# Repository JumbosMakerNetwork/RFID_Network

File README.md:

# Jumbo's Maker Network - RFID Usage Tracking
This project is an RFID tag and arduino based system for tracking use in a makerspace while also integrating automated safety interlocks through use of data and power relays. 

This includes the firmware and hardware files for the system as well as a series of analytical software used to derive insightful data from the makerspace.

This project is currently in development, so if you stumble across this, please let us know if something doesn't work and feel free to comment to help out if you have some useful feedback.

## Hardware
Contains:
	-Eagle Files, used as design for fabricating circuit boards. There are a variety of circuit boards used in this project, the principal ones being a data interlock board used to interrupt serial communication between devices, and a Pro Shield board, which is used to connect all the components of the RFID reader (e.g. the Mifare Scanner, the LCD monitor..) to the Arduino ESP8266
	-Enclosure files, which are CAD schematics for 3d printing/laser cutting the enclosure that holds all the components

## Scripts
Contains:
	-Several scripts used to initialize new stations and users. These funcitons will eventually be encapsulated by a unified Python data model which will be used for all SQL functions.

## Source Code
Contains:
	-Arduino: the necessary libraries and source code needed for the Arduino microcontrollers powering this system. Within this repo are folders for Signin and Relay stations; Signin stations only have the funcitnality of signin/signout, whereas the relay terminals are capable of restricting power or serial communication between devices.
	-All the php and PSQL initialization tools used to create our PSQL database (in scripts and www)

## Web Analytics
Contains:
	-a set of documents that generate an HTML page featuring visualized data of makerspace usage and new membership over time. This data is collected with python scripts using the pyscopg module, and then interpreted with javascript files utilizing ajax and jquery, finally being visualized with the charts.js library.

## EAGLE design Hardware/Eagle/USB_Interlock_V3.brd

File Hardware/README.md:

# CEEO Makerspace Data Collection - Hardware

## Description
This will be for all the drawings for RFID fobs, terminal enclosures, and PCBs that support the system. 

## To Dos
- ~~ Design Enclosures ~~
- ~~ Finish PCBs ~~
- ~~ Design some RFID key fobs ~~
- ~~ Add Bill of Materials ~~

## Notes

Notes go here

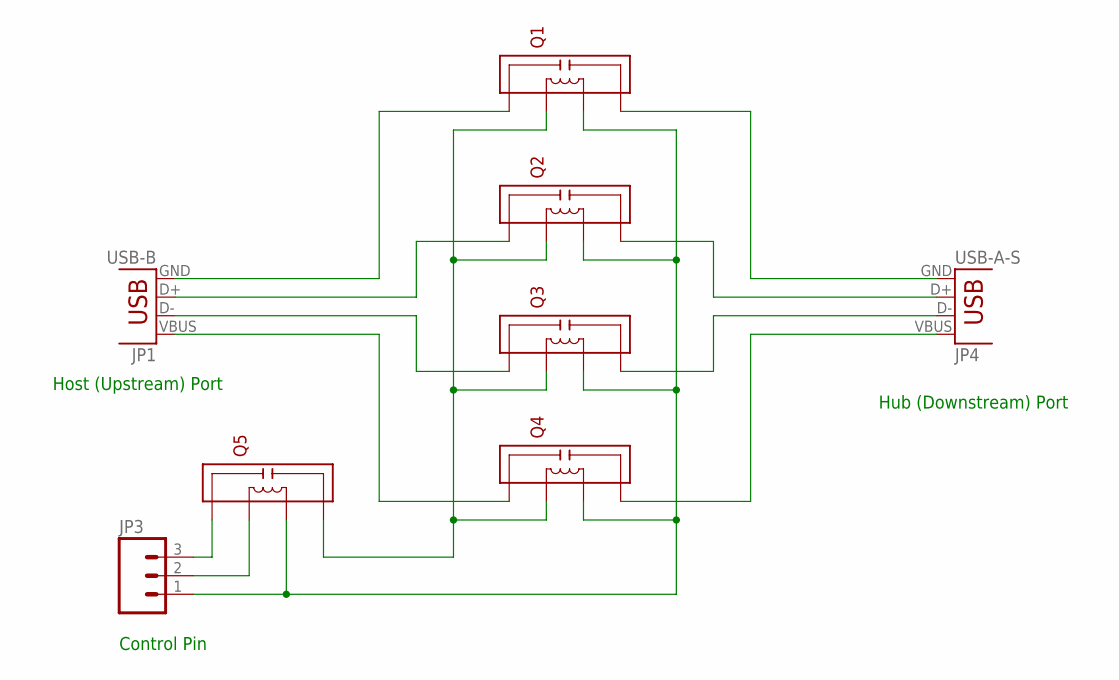
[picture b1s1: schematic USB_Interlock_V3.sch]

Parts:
JP1: USB-B; USB-B-PTH
JP3: M03LONGPADS; 1X03_LONGPADS
JP4: USB-A-S
Q1, Q2, Q3, Q4, Q5: 9007-12-01

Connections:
GND: JP3.1, Q1.P$3, Q2.P$3, Q3.P$3, Q4.P$3, Q5.P$3
HV1: JP4.D-, Q3.P$4
HV2: JP4.D+, Q2.P$4
LV1: JP1.D-, Q3.P$1
LV2: JP1.D+, Q2.P$1
unnamed: JP3.3, Q5.P$1
unnamed: JP3.2, Q5.P$2
unnamed: Q1.P$2, Q2.P$2, Q3.P$2, Q4.P$2, Q5.P$4
unnamed: JP1.GND, Q1.P$1
unnamed: JP4.GND, Q1.P$4
unnamed: JP1.VBUS, Q4.P$1
V1: JP4.VBUS, Q4.P$4

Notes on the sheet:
Hub (Downstream) Port
Host (Upstream) Port
Control Pin

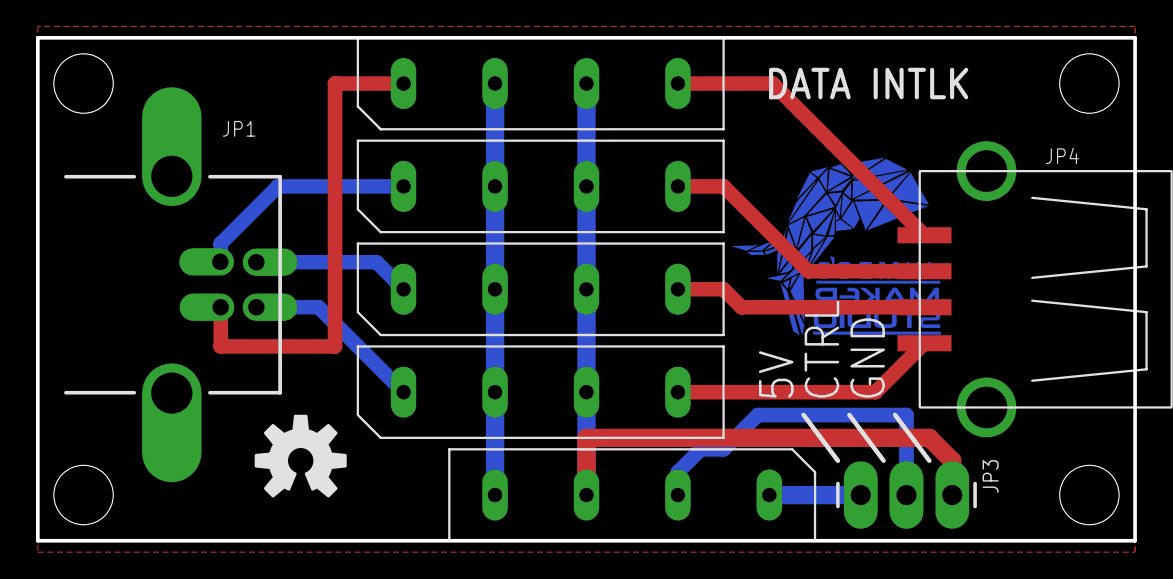
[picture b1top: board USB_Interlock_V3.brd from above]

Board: 2 copper layers, 61.0 x 27.9 mm, 14 parts (1 on the bottom side), 12 nets.

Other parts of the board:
U$1: OSHW-LOGO-M
U$2, U$3, U$4, U$5: STAND-OFF
U$7: JMS_LOG_COPPER

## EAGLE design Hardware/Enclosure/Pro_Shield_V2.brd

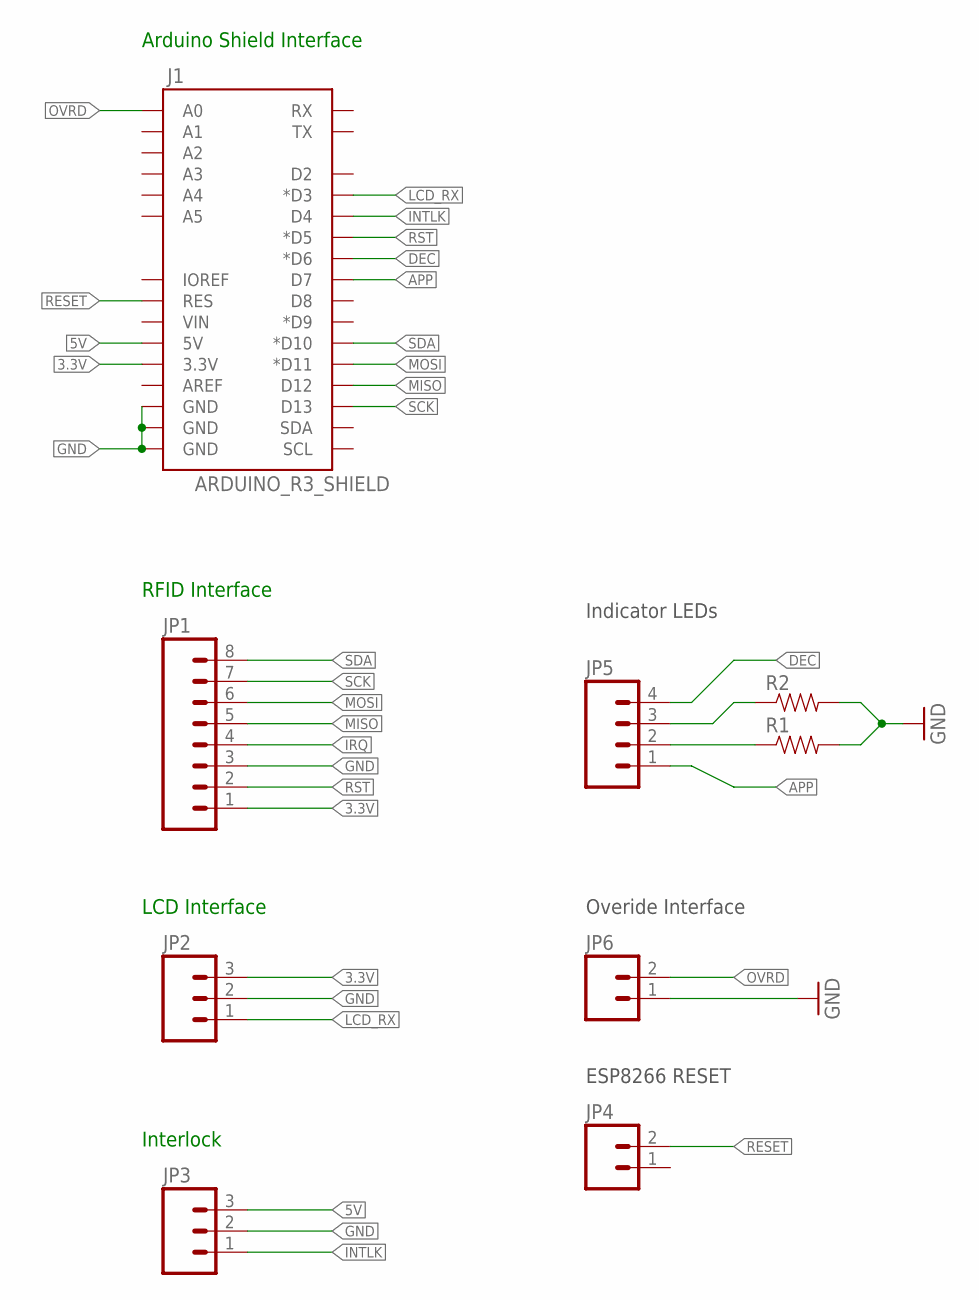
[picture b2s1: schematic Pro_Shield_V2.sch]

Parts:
J1: ARDUINO_R3_SHIELD; UNO_R3_SHIELD
JP1: M08LONGPADS; 1X08_LONGPADS
JP2, JP3: M03LONGPADS; 1X03_LONGPADS
JP4, JP6: M02LOCK_LONGPADS; 1X02_LOCK_LONGPADS
JP5: M04LONGPADS; 1X04_LONGPADS
R1, R2: RESISTORPTH-1/4W; AXIAL-0.4

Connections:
3.3V: J1.3.3V, JP1.1, JP2.3
5V: J1.5V, JP3.3
APP: J1.D7, JP5.1
DEC: J1.D6 (*D6), JP5.4
GND: J1.GND@0 (GND), J1.GND@1 (GND), J1.GND@2 (GND), JP1.3, JP2.2, JP3.2, JP6.1, R1.P$2 (2), R2.P$2 (2)
INTLK: J1.D4, JP3.1
IRQ: JP1.4
LCD_RX: J1.D3 (*D3), JP2.1
MISO: J1.D12, JP1.5
MOSI: J1.D11 (*D11), JP1.6
unnamed: JP5.2, R1.P$1 (1)
unnamed: JP5.3, R2.P$1 (1)
OVRD: J1.A0, JP6.2
RESET: J1.RES, JP4.2
RST: J1.D5 (*D5), JP1.2
SCK: J1.D13, JP1.7
SDA: J1.D10 (*D10), JP1.8

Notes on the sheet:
LCD Interface
RFID Interface
Arduino Shield Interface
Indicator LEDs
Overide Interface
Interlock
ESP8266 RESET

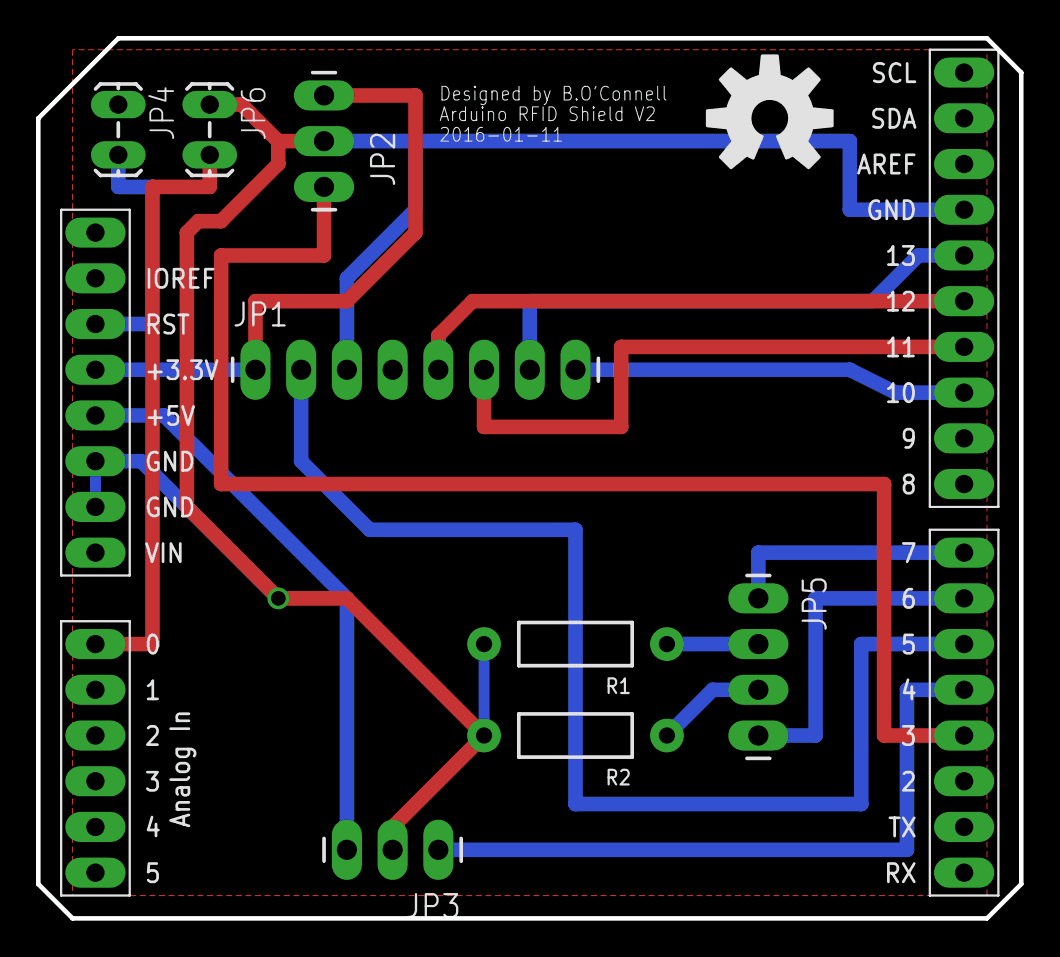
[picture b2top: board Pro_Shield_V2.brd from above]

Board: 2 copper layers, 54.6 x 48.9 mm, 10 parts (0 on the bottom side), 16 nets.

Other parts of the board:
U$1: OSHW-LOGO-L

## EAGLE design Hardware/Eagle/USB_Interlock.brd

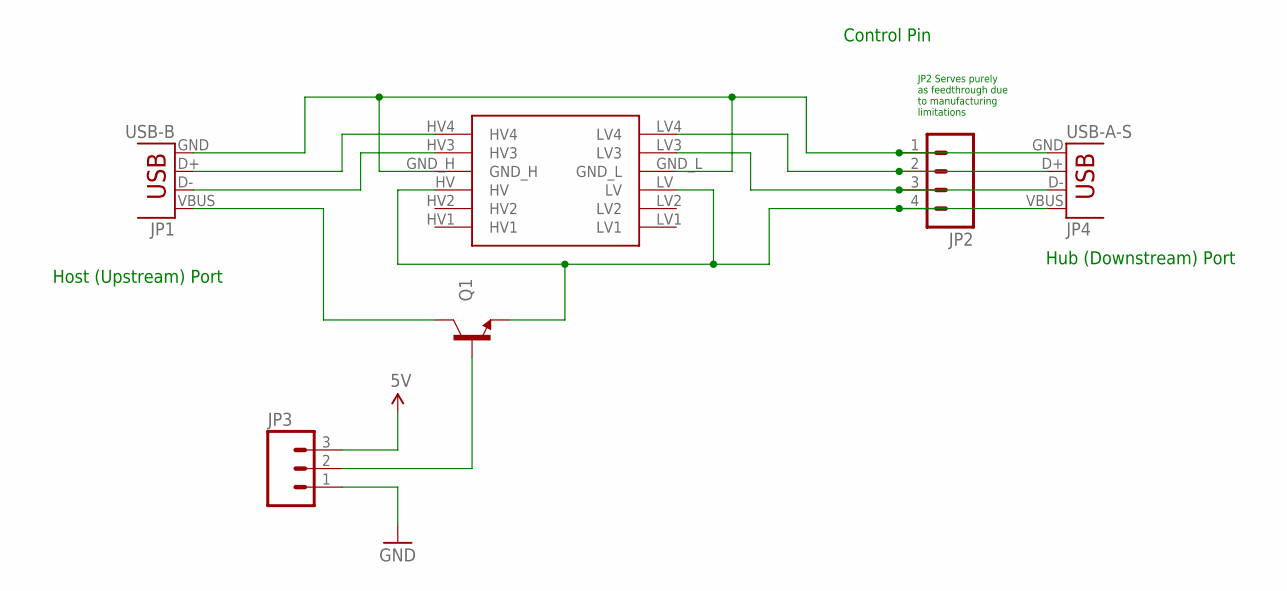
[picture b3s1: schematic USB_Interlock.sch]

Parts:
JP1: USB-B; USB-B-PTH
JP2: M04LONGPADS; 1X04_LONGPADS
JP3: M03LONGPADS; 1X03_LONGPADS
JP4: USB-A-S
Q1: TRANSISTOR_NPNBC547; TO-92-AMMO
U$1: LOGIC_LEVEL_CONVERTER

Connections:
5V: JP3.3
CTRL: JP3.2, Q1.2 (B)
GND: JP1.GND, JP2.1, JP3.1, JP4.GND, U$1.GND_H, U$1.GND_L
unnamed: JP2.4, JP4.VBUS, Q1.3 (E), U$1.HV, U$1.LV
unnamed: JP2.2, JP4.D+, U$1.LV4
unnamed: JP2.3, JP4.D-, U$1.LV3
unnamed: JP1.D+, U$1.HV4
unnamed: JP1.D-, U$1.HV3
unnamed: JP1.VBUS, Q1.1 (C)

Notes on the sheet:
Hub (Downstream) Port
Host (Upstream) Port
Control Pin
JP2 Serves purely as feedthrough due to manufacturing limitations

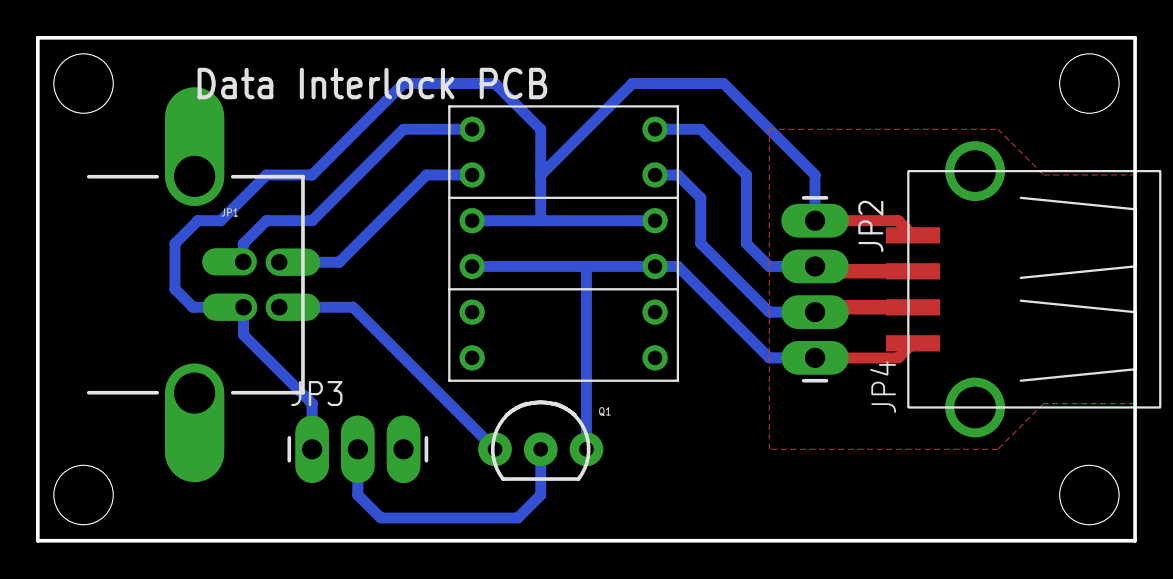
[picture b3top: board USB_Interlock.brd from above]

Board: 2 copper layers, 61.0 x 27.9 mm, 10 parts (0 on the bottom side), 8 nets.

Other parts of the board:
U$2, U$3, U$4, U$5: STAND-OFF

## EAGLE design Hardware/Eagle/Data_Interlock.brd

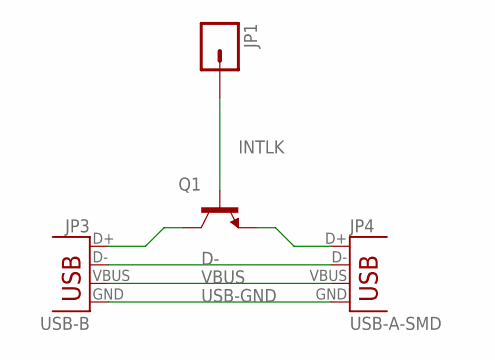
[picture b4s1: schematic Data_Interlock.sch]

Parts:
JP1: M01PTH_LONGPAD; 1X01_LONGPAD
JP3: USB-B; USB-B-PTH
JP4: USB-A-SMD; USB-A-S-NOSILK-FEMALE
Q1: TRANSISTOR_NPNBC547; TO-92-AMMO

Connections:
D-: JP3.D-, JP4.D-
INTLK: JP1.1, Q1.2 (B)
unnamed: JP3.D+, Q1.1 (C)
unnamed: JP4.D+, Q1.3 (E)
USB-GND: JP3.GND, JP4.GND
VBUS: JP3.VBUS, JP4.VBUS

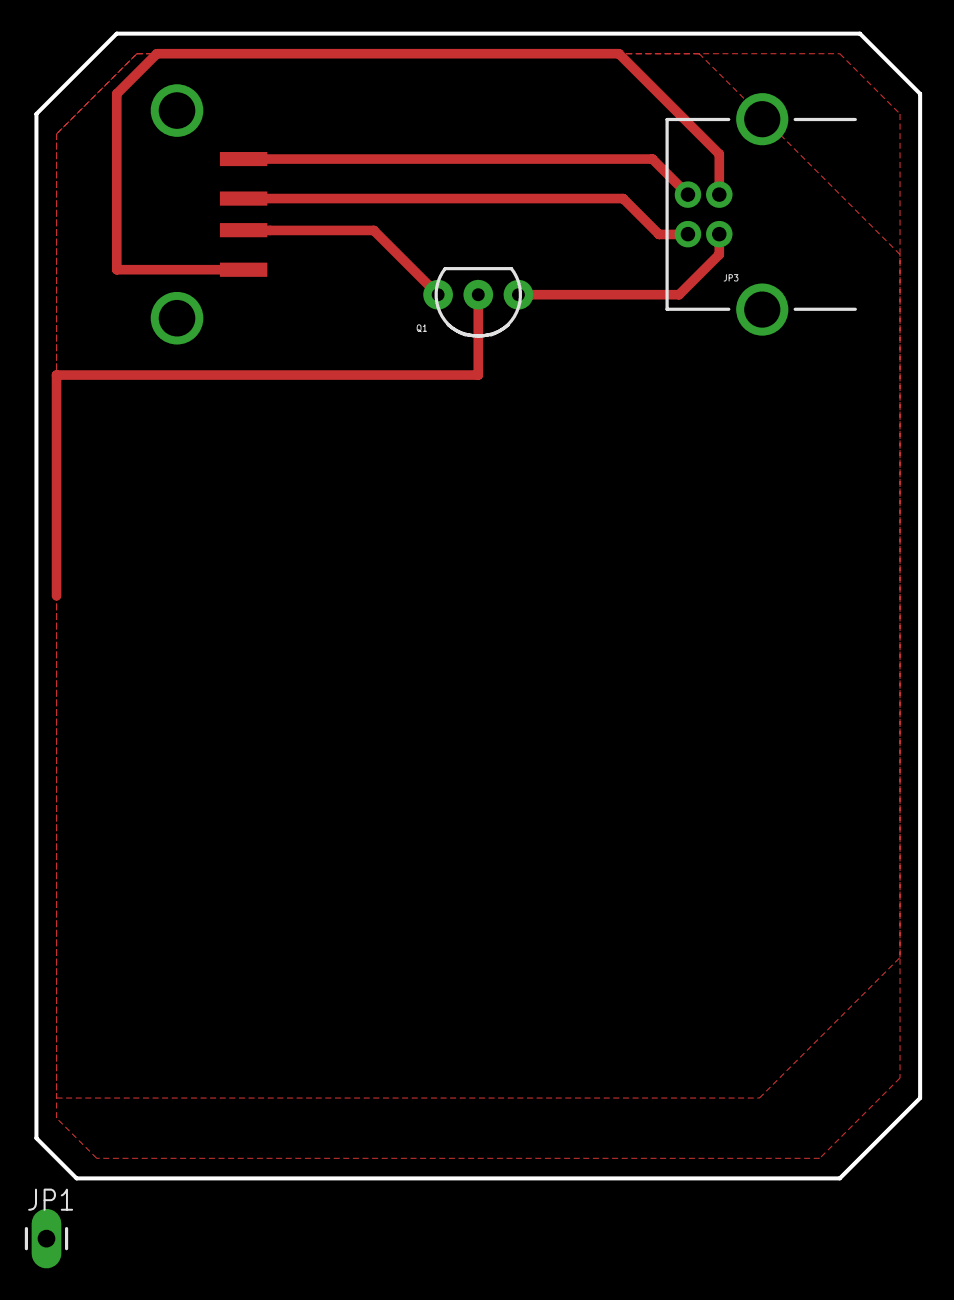
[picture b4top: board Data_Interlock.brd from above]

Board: 2 copper layers, 55.9 x 72.4 mm, 4 parts (0 on the bottom side), 6 nets.

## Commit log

2015-07-29 new file: RFID_Network/.DS_Store new file: RFID_Network/Hardware/.DS_Store new file: RFID_Network/Hardware/Eagle/Arduino_Shield.b#1 new file: RFID_Network/Hardware/Eagle/Arduino_Shield.b#2 new file: 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
2015-07-29 Deleted old eagle files
2015-07-29 This stupid thing deleted everything. Trying to add them back.
2015-07-29 Added more files for reference and development
2015-07-29 Added more readm files for reference
2015-07-29 Updating table setup
2015-08-02 Updating SignIn station
2015-08-03 Updated SignIn code to fix the multi read error and to function with the RFID.php and the new hex format for the ID.
2015-08-03 Aug 3: added LCD, LED displays, error handling and syntax fixes
2015-08-03 removing debug report file
2015-08-05 adding enclosure models repo, and signin enclosure design STL files
2015-08-05 enclosure modification
2015-08-05 enclosure files and software debug
2015-08-06 Moving things into the appropriate folders
2015-08-06 Added assembly of signin station
2015-08-10 DS Store
2015-08-17 Adding altered libraries
2015-08-17 Updating Pure_ESP8266 functions document
2015-08-19 updating signin.pde and adding relays.pde
2015-09-02 adding basic python script
2015-09-02 minor changes
2015-09-07 final versions of signin and relay software, sept 7
2015-10-01 Scripts and 'no id in db' timer fix
2015-10-08 adding 30second access relay
2015-11-12 updating with pro-shield
2016-01-11 Updating EAGLE files
2016-01-22 New boards, terminal enclosures, and labview interface
    Former-commit-id: 246ca6c8f016e846ca299188d99d46875b994b37
2016-01-22 creating gh-pages branch
2016-01-22 test
2016-01-22 adding www analytics directoty
2016-01-22 adding web analytics directoty
2016-01-22 new ajax req format
2016-01-22 moving main.js
2016-01-22 async
2016-01-22 string method removed
2016-01-24 new py script which writes to a .txt file
2016-01-24 updating js to pull from .txt
2016-01-24 debug1
2016-01-24 debug2
2016-01-24 debug3
2016-01-24 debug4
2016-01-24 adding context
2016-01-24 print array
2016-01-24 debug 7
2016-01-24 adding user tracking
2016-01-24 adding second dataset
2016-01-27 merging
2016-01-27 General Updates. GIT needs a clean which is forthcoming.
    Former-commit-id: 5bcd1b9d70129efe4d0fc99a3c9c71a42921daf1
2016-01-27 General Updates. GIT needs a clean which is forthcoming.
    Former-commit-id: abd0b8c7047a3f165c754e3a35e95ee914083049
2016-01-27 General Updates. GIT needs a clean which is forthcoming.
    Former-commit-id: 52de6ff199629053957ccf6bc6cdfeb7a5049229
2016-01-27 Pushing Local Modifications
2016-01-27 General updates
    Former-commit-id: e108daf6675cec777fa80f58d722c8056431356f
2016-01-27 Updating relay.pde. Correcting GET discrepency with rfid.php
    Former-commit-id: b77238e92873a3ff46766ce028b5121678333ddf
2016-01-27 File Cleanup
    Former-commit-id: ab2dfde575aa20bc2a914815df67f4b92a4f16c1
2016-01-27 File Cleanup
    Former-commit-id: 87f29da8ebd533920e39b83dba444b9a10ae08c1
2016-01-28 adding 'create permissions for all' script
2016-01-29 labels
2016-01-29 graph size reduction
2016-01-29 slight code correction
2016-01-29 php compatible
2016-02-01 Update to arduino stuff for LCD fix. More to come.
    Former-commit-id: 047aca626a60cc439cf33ff01ea01eedb341d17f
2016-02-02 tidying relays.pde and adding lcd_init fxn
2016-02-08 relays
2016-02-21 adding data model
2016-03-21 data-model
2016-03-21 deleting old repo
2016-03-22 removing old files
2016-03-22 Updating Eagle Files for compatibility
2016-03-22 updating readme
2016-06-06 adding v1 bray roll call javascript
2016-06-06 parsing error
2016-06-06 undefined attributes
2016-06-06 undefined attributes as index
2016-06-06 flushing page
2016-06-06 adding color'
2016-06-06 default bug
2016-06-07 python edit
2016-06-09 minor updates
    Former-commit-id: 005f154041ac5a9cfd41a52d4b3ff765475395c9
2016-06-09 roll edits
2016-06-30 graph data updates
2016-06-30 updating user signups
2016-06-30 pushing after usage log backup
2016-06-30 expanding graph
2016-06-30 coloring and shortening graph
2016-06-30 dont display last two elements
2016-06-30 adding more stuff
2016-06-30 moving stuff
2016-07-05 general updates
    Former-commit-id: dbd0c8fdd2fce02a2d89b31192be62baceb01c1c
2016-07-05 Computer Interlock upload
    Former-commit-id: 4864705738b9b1c89b03139906ac93d3cc167db9
2016-07-05 refreshing src code
2016-07-06 Added backup of relay due to weirdness to be figured out later
2016-07-06 utilizing curl functions
2016-07-06 adding wokring python relay files
2016-07-06 curl req to django
2016-07-13 updating new wifi names
2016-07-14 computer interlock updates
2016-08-10 updating Raspberry Pi Source code in Source_Code/RFID_C
2016-08-11 Updating Computer interlock and some hardware

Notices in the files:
parts and their libraries:
SparkFun-Connectors: Licensing: Creative Commons ShareAlike 4.0 International - https://creativecommons.org/licenses/by-sa/4.0
